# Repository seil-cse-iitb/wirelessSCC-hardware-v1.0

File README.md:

# Wireless SCC Hardware

The hardware for the SCCs is designed in **Ki-CAD**. This particular folder contains design for the *actuation node* which are deployed in SCCs. 

Actuation nodes control lights, fans and ACs. They are designed in such a way that they can be directly mounted on an 8-channel relay board in order to reduce footprint of the hardware. At max the node can connect to 12 appliances. 

The folder are explained as follows: 

1. *footprints* : Contains footprints for all the necessary components.
2. *libraries* : Contains libraries required for the project. The folder also contains some custom made libraries. Pls, see this tutorial on how to [make and add custom component in Ki-CAD](https://www.google.com/search?client=ubuntu&channel=fs&q=add+custom+components+in+kicad&ie=utf-8&oe=utf-8#kpvalbx=1).

Other files contain schematic and pcb file of the hardware.

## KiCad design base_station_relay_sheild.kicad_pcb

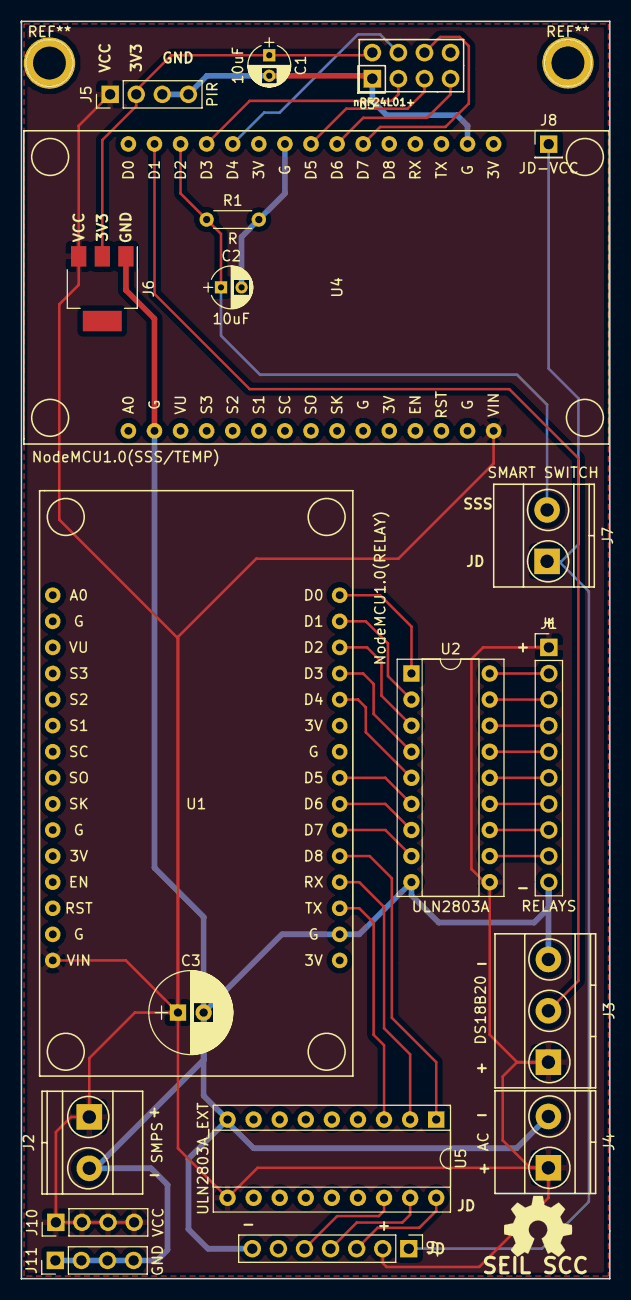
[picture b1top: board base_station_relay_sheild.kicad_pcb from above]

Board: 2 copper layers, 57.3 x 122.4 mm, 20 parts (0 on the bottom side), 33 nets.

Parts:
C1, C2: 10uF; CP_Radial_D4.0mm_P2.00mm
C3: 470uF; CP_Radial_D8.0mm_P2.50mm
J1: RELAYS; Socket_Strip_Straight_1x10_Pitch2.54mm
J2: SMPS; TerminalBlock_Pheonix_MKDS1.5-2pol
J3: DS18B20; TerminalBlock_Pheonix_MKDS1.5-3pol
J4: AC; TerminalBlock_Pheonix_MKDS1.5-2pol
J5: PIR; Socket_Strip_Straight_1x04_Pitch2.54mm
J6: 3V3 REG; SOT-223
J7: SMART SWITCH; TerminalBlock_Pheonix_MKDS1.5-2pol
J8: JD-VCC; Socket_Strip_Straight_1x01_Pitch2.54mm
J9: 4_RELAY_EXTENSION; Socket_Strip_Straight_1x07_Pitch2.54mm
J10: VCC; Socket_Strip_Straight_1x04_Pitch2.54mm
J11: GND; Socket_Strip_Straight_1x04_Pitch2.54mm
R1: R; R_Axial_DIN0204_L3.6mm_D1.6mm_P5.08mm_Horizontal
U1: NodeMCU1.0(RELAY); NodeMCU1.0(12-E)
U2: ULN2803A; DIP-18_W7.62mm_Socket
U3: nRF24L01+; NRF24L01
U4: NodeMCU1.0(SSS/TEMP); NodeMCU1.0(12-E)
U5: ULN2803A_EXT; DIP-18_W7.62mm_Socket

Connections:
/3V3: C1.1, J5.2, J6.2, U3.2, U4.11, U4.16, U4.25
/CE: U3.3, U4.27
/CSN: U3.4, U4.26
/GND: C1.2, C2.2, C3.2, J1.10, J2.2, J3.3, J4.2, J5.3, J5.4, J6.1, J9.7, J11.1, J11.2, J11.3, J11.4, R1.2, U1.2, U1.10, U1.14, U1.17, U1.24, U2.9, U3.1, U4.2, U4.10, U4.14, U4.17, U4.24, U5.9
/IN1: U1.30, U2.1
/IN2: U1.29, U2.2
/IN3: U1.28, U2.3
/IN4: U1.27, U2.4
/IN5: U1.26, U2.5
/IN6: U1.23, U2.6
/IN7: U1.22, U2.7
/IN8: U1.21, U2.8
/IN9: U1.20, U5.1
/IN10: U1.19, U5.2
/IN11: U1.18, U5.3
/JD-VCC: J7.1, J8.1, J9.1
/MISO: U3.7, U4.22
/MOSI: U3.6, U4.21
/OneWire: J3.2, U4.29
/R1: J1.2, U2.18
/R2: J1.3, U2.17
/R3: J1.4, U2.16
/R4: J1.5, U2.15
/R5: J1.6, U2.14
/R6: J1.7, U2.13
/R7: J1.8, U2.12
/R8: J1.9, U2.11
/R9: J9.3, U5.18
/R10: J9.4, U5.17
/R11: J9.5, U5.16
/SCK: U3.5, U4.23
/STATUS: C2.1, J7.2, R1.1, U4.28
/VCC: C3.1, J1.1, J2.1, J3.1, J4.1, J5.1, J6.3, J9.2, J10.1, J10.2, J10.3, J10.4, U1.15, U2.10, U4.15, U5.10

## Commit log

2017-08-27 Uploaded README file
2017-08-28 SCC PCB Schematic
2017-08-28 SCC PCB footprint
2017-08-28 Necessary footprints
2017-08-28 Necessary library files
2017-08-28 SCC PCB image file
2019-06-06 Updated README file
